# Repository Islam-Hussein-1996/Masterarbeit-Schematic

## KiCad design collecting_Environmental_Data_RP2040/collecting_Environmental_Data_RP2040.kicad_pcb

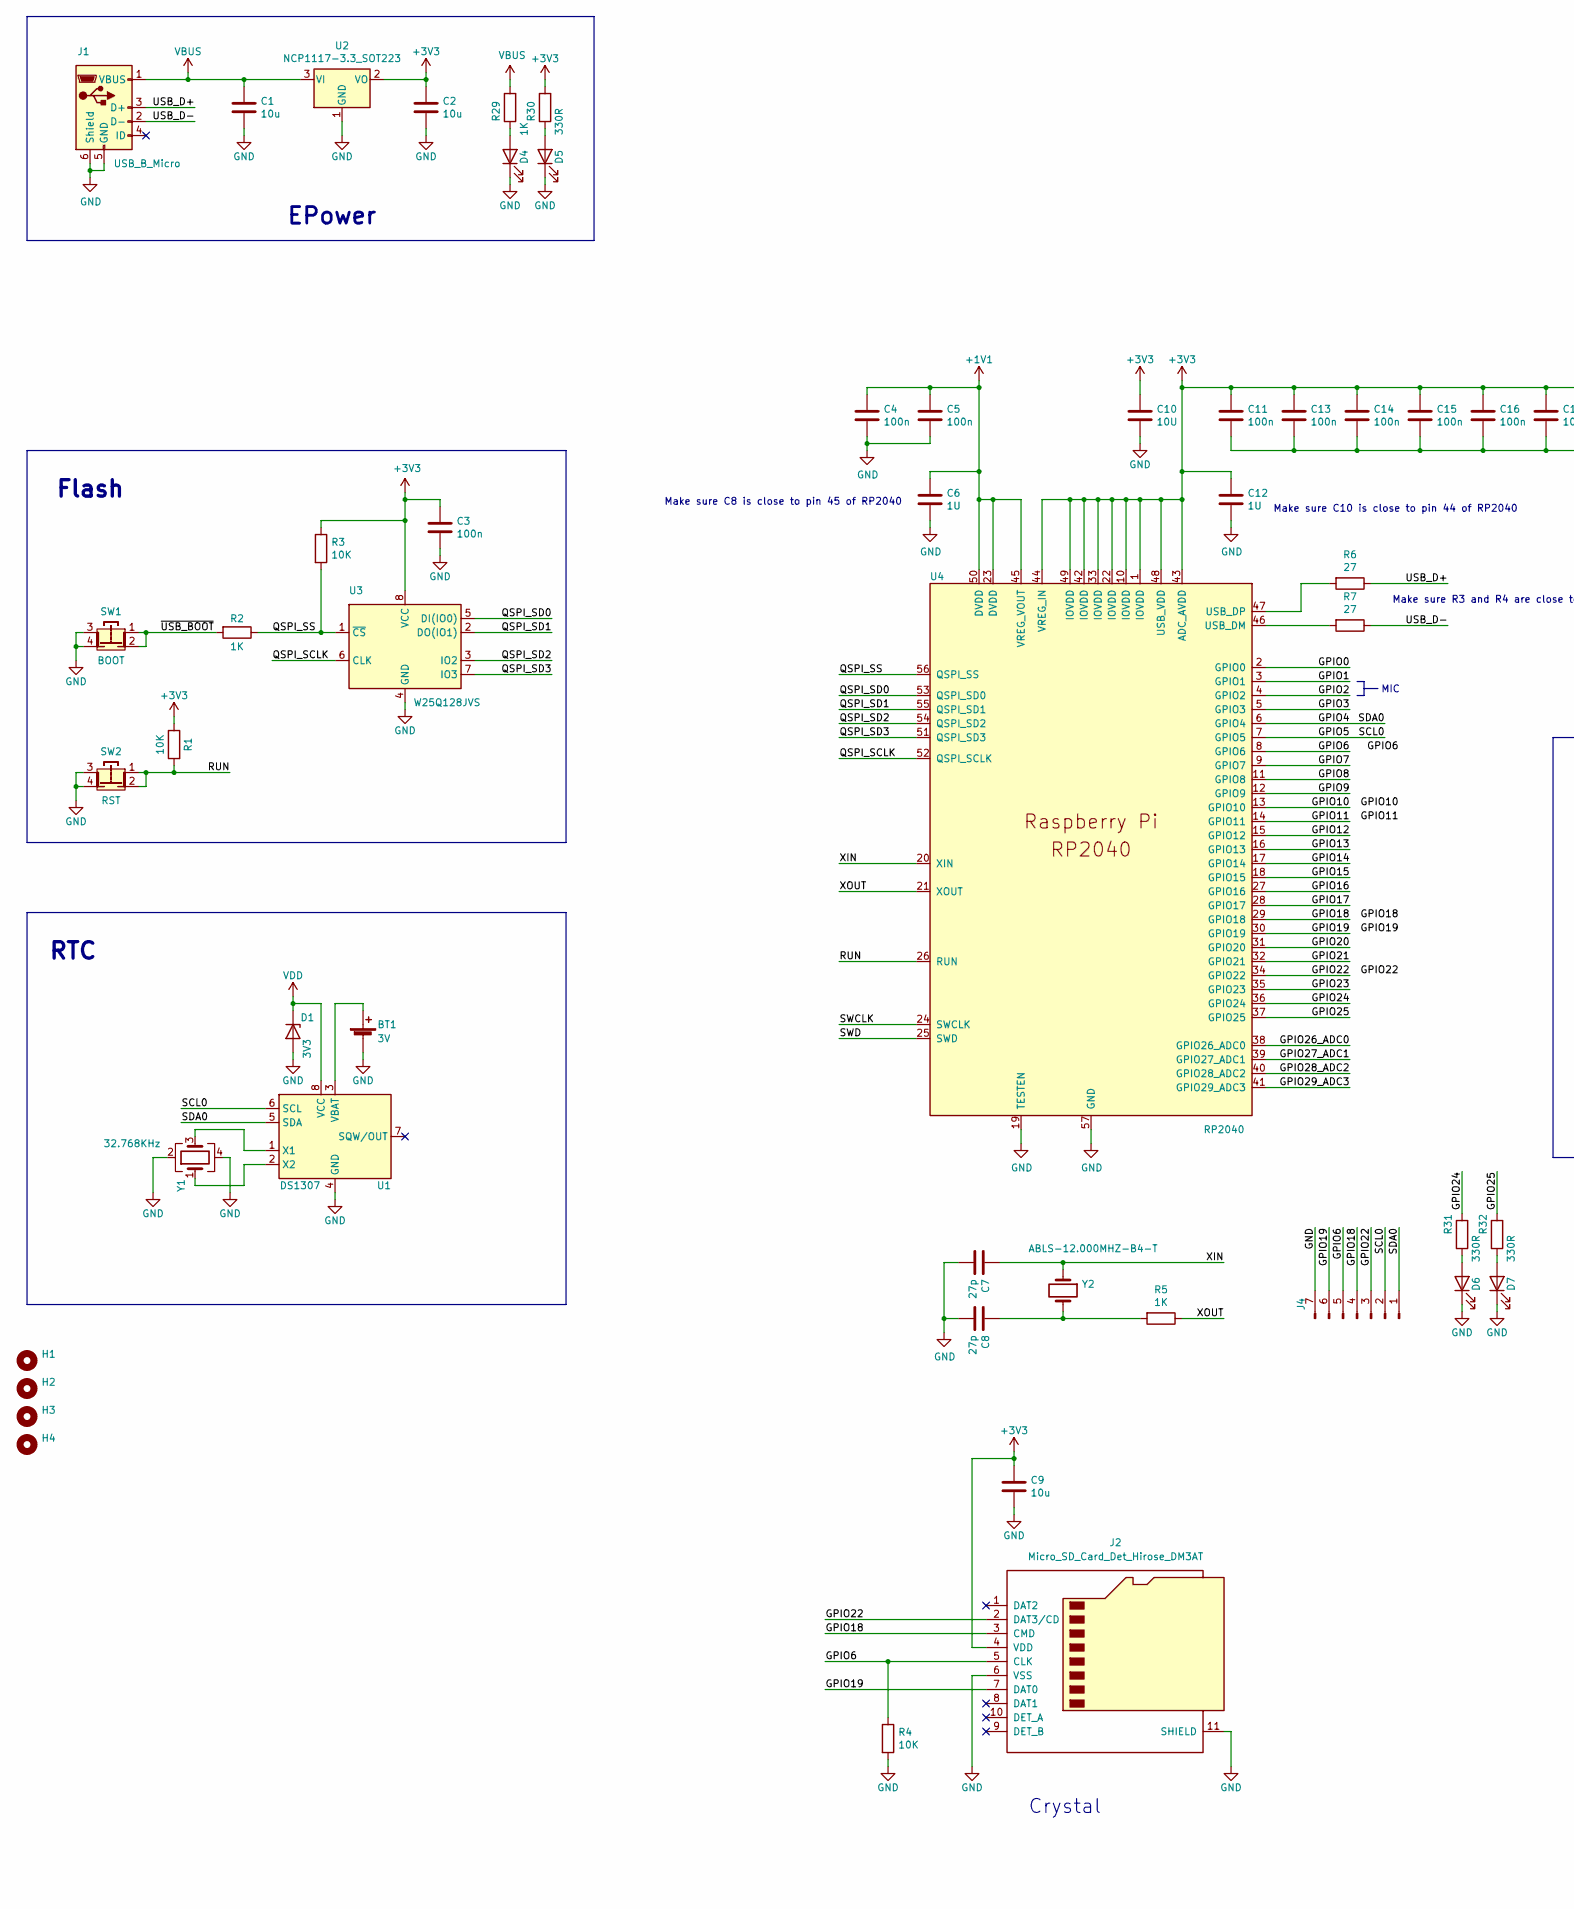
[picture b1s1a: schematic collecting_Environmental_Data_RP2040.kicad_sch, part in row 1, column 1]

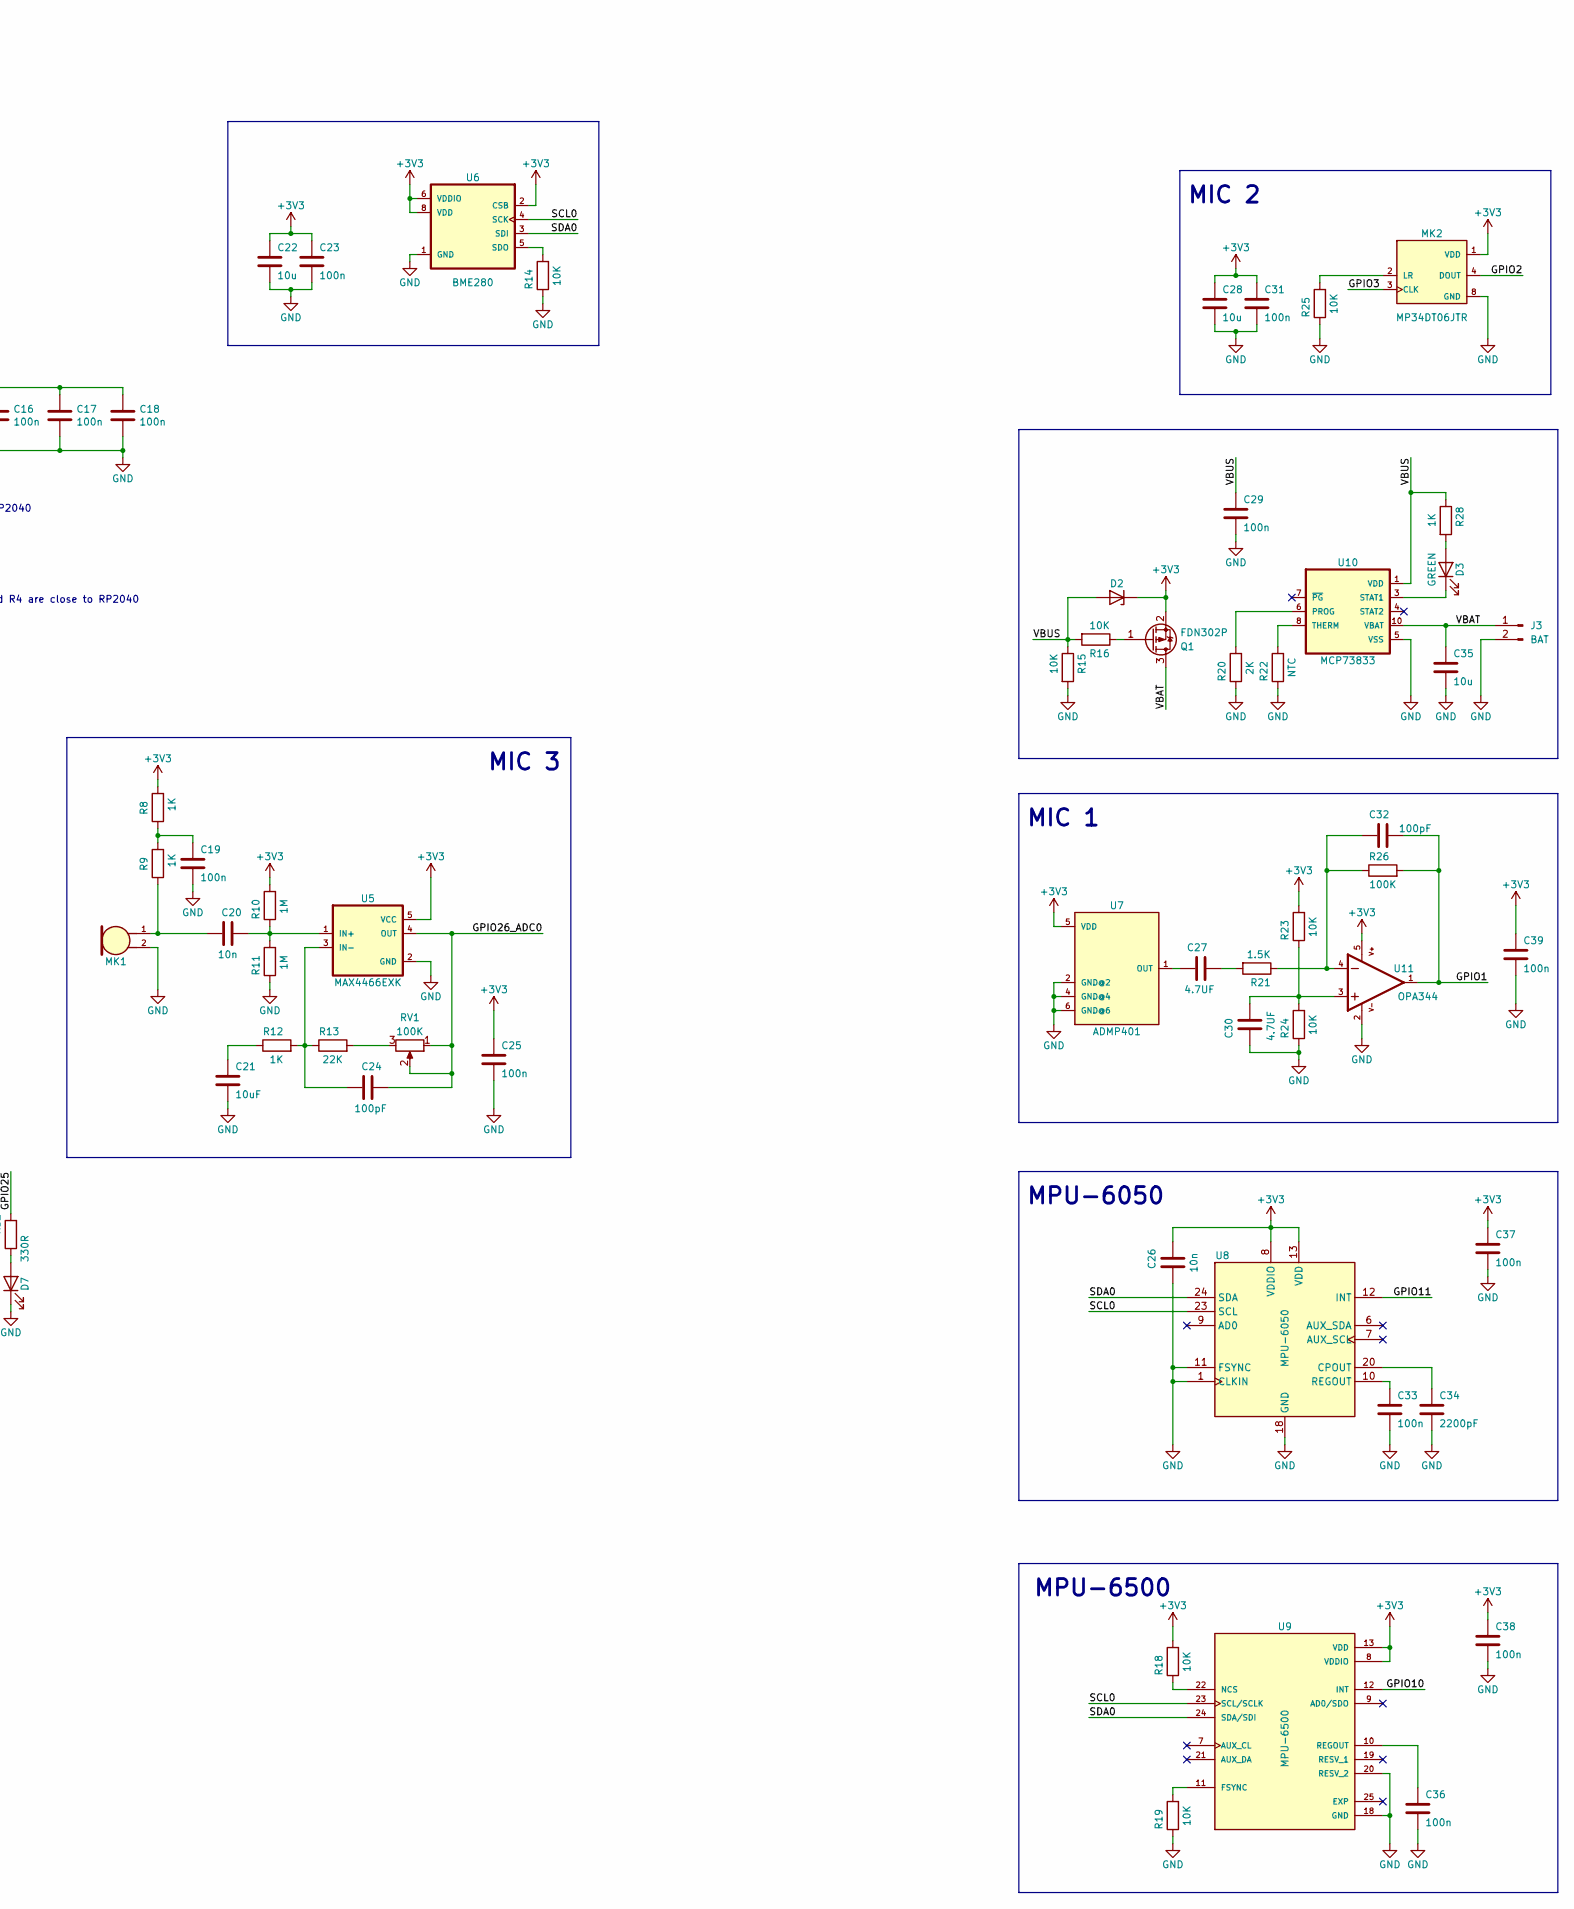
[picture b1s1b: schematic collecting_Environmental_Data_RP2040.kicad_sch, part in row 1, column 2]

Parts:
BT1: 3V; PinHeader_1x02_P2.54mm_Vertical
C1, C2, C9, C22, C28, C35: 10u; C_0805_2012Metric_Pad1.18x1.45mm_HandSolder
C3, C4, C5, C11, C13, C14, C15, C16, C17, C18, C19, C23, C25, C29, C31, C33, C36, C37, C38, C39: 100n; C_0603_1608Metric_Pad1.08x0.95mm_HandSolder
C6, C12: 1U; C_0603_1608Metric_Pad1.08x0.95mm_HandSolder
C7, C8: 27p; C_0603_1608Metric_Pad1.08x0.95mm_HandSolder
C10: 10U; C_0805_2012Metric_Pad1.18x1.45mm_HandSolder
C20, C26: 10n; C_0603_1608Metric_Pad1.08x0.95mm_HandSolder
C21: 10uF; C_0805_2012Metric_Pad1.18x1.45mm_HandSolder
C24, C32: 100pF; C_0603_1608Metric_Pad1.08x0.95mm_HandSolder
C27, C30: 4.7UF; C_0603_1608Metric_Pad1.08x0.95mm_HandSolder
C34: 2200pF; C_0603_1608Metric_Pad1.08x0.95mm_HandSolder
D1: 3V3; D_SOD-123
D2: D_Zener; D_SOD-123
D3: GREEN; LED_0805_2012Metric_Pad1.15x1.40mm_HandSolder
D4, D5, D6, D7: LED; LED_0805_2012Metric_Pad1.15x1.40mm_HandSolder
H1, H2, H3, H4: MountingHole; MountingHole_2.7mm_M2.5
J1: USB_B_Micro; USB_Micro-B_Molex-105017-0001
J2: Micro_SD_Card_Det_Hirose_DM3AT; microSD_HC_Molex_104031-0811
J3: BAT; PinHeader_1x02_P2.54mm_Vertical
J4: Conn_01x07_Male; PinHeader_1x07_P2.54mm_Vertical
MK1: CMA-4544PF-W; MIC_CMA-4544PF-W
MK2: MP34DT06JTR; MIC_MP34DT06JTR
Q1: FDN302P; SOT-23
R1, R3, R4, R14, R15, R16, R18, R19, R23, R24, R25: 10K; R_0603_1608Metric_Pad0.98x0.95mm_HandSolder
R2, R5, R8, R9, R12, R28, R29: 1K; R_0603_1608Metric_Pad0.98x0.95mm_HandSolder
R6, R7: 27; R_0603_1608Metric_Pad0.98x0.95mm_HandSolder
R10, R11: 1M; R_0603_1608Metric_Pad0.98x0.95mm_HandSolder
R13: 22K; R_0603_1608Metric_Pad0.98x0.95mm_HandSolder
R20: 2K; R_0603_1608Metric_Pad0.98x0.95mm_HandSolder
R21: 1.5K; R_0603_1608Metric_Pad0.98x0.95mm_HandSolder
R22: NTC; R_0603_1608Metric_Pad0.98x0.95mm_HandSolder
R26: 100K; R_0603_1608Metric_Pad0.98x0.95mm_HandSolder
R30, R31, R32: 330R; R_0603_1608Metric_Pad0.98x0.95mm_HandSolder
RV1: 100K; Potentiometer_Bourns_TC33X_Vertical
SW1: BOOT; SW_Push_4X4mm
SW2: RST; SW_Push_4X4mm
U1: DS1307; SOIC-8_3.9x4.9mm_P1.27mm
U2: NCP1117-3.3_SOT223; SOT-223-3_TabPin2
U3: W25Q128JVS; SOIC-8_5.23x5.23mm_P1.27mm
U4: RP2040; RP2040-QFN-56
U5: MAX4466EXK; SOT-353_SC-70-5
U6: BME280
U7: ADMP401
U8: MPU-6050; InvenSense_QFN-24_4x4mm_P0.5mm
U9: MPU-6500; QFN40P300X300X95-25N
U10: MCP73833; MSOP-10_3x3mm_P0.5mm
U11: OPA344; SOT-23-5
Y1: 32.768KHz
Y2: ABLS-12.000MHZ-B4-T; Crystal_SMD_ECS_CSM3X-2Pin_7.6x4.1mm

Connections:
+1V1: C4.1, C5.1, C6.1, U4.23 (DVDD), U4.45 (VREG_VOUT), U4.50 (DVDD)
+3V3: C2.1, C3.1, C9.1, C10.1, C11.1, C12.1, C13.1, C14.1, C15.1, C16.1, C17.1, C18.1, C22.1, C23.1, C25.1, C26.1, C28.1, C31.1, C37.1, C38.1, C39.1, D2.1 (K), J2.4 (VDD), MK2.1 (VDD), Q1.2 (S), R1.1, R3.1, R8.2, R10.2, R18.2, R23.2, R30.2, U2.2 (VO), U3.8 (VCC), U4.1 (IOVDD), U4.10 (IOVDD), U4.22 (IOVDD), U4.33 (IOVDD), U4.42 (IOVDD), U4.43 (ADC_AVDD), U4.44 (VREG_IN), U4.48 (USB_VDD), U4.49 (IOVDD), U5.5 (VCC), U6.2 (CSB), U6.6 (VDDIO), U6.8 (VDD), U7.5 (VDD), U8.8 (VDDIO), U8.13 (VDD), U9.8 (VDDIO), U9.13 (VDD), U11.5
/GPIO0: U4.2 (GPIO0)
/GPIO1: C32.2, R26.2, U4.3 (GPIO1), U11.1
/GPIO2: MK2.4 (DOUT), U4.4 (GPIO2)
/GPIO3: MK2.3 (CLK), U4.5 (GPIO3)
/GPIO4: J4.1, U1.5 (SDA), U4.6 (GPIO4), U6.3 (SDI), U8.24 (SDA), U9.24 (SDA/SDI)
/GPIO5: J4.2, U1.6 (SCL), U4.7 (GPIO5), U6.4 (SCK), U8.23 (SCL), U9.23 (SCL/SCLK)
/GPIO6: J2.5 (CLK), J4.5, R4.1, U4.8 (GPIO6)
/GPIO7: U4.9 (GPIO7)
/GPIO8: U4.11 (GPIO8)
/GPIO9: U4.12 (GPIO9)
/GPIO10: U4.13 (GPIO10), U9.12 (INT)
/GPIO11: U4.14 (GPIO11), U8.12 (INT)
/GPIO12: U4.15 (GPIO12)
/GPIO13: U4.16 (GPIO13)
/GPIO14: U4.17 (GPIO14)
/GPIO15: U4.18 (GPIO15)
/GPIO16: U4.27 (GPIO16)
/GPIO17: U4.28 (GPIO17)
/GPIO18: J2.3 (CMD), J4.4, U4.29 (GPIO18)
/GPIO19: J2.7 (DAT0), J4.6, U4.30 (GPIO19)
/GPIO20: U4.31 (GPIO20)
/GPIO21: U4.32 (GPIO21)
/GPIO22: J2.2 (DAT3/CD), J4.3, U4.34 (GPIO22)
/GPIO23: U4.35 (GPIO23)
/GPIO24: R31.2, U4.36 (GPIO24)
/GPIO25: R32.2, U4.37 (GPIO25)
/GPIO26_ADC0: C24.1, RV1.1, RV1.2, U4.38 (GPIO26_ADC0), U5.4 (OUT)
/GPIO27_ADC1: U4.39 (GPIO27_ADC1)
/GPIO28_ADC2: U4.40 (GPIO28_ADC2)
/GPIO29_ADC3: U4.41 (GPIO29_ADC3)
/QSPI_SCLK: U3.6 (CLK), U4.52 (QSPI_SCLK)
/QSPI_SD0: U3.5 (DI(IO0)), U4.53 (QSPI_SD0)
/QSPI_SD1: U3.2 (DO(IO1)), U4.55 (QSPI_SD1)
/QSPI_SD2: U3.3 (IO2), U4.54 (QSPI_SD2)
/QSPI_SD3: U3.7 (IO3), U4.51 (QSPI_SD3)
/QSPI_SS: R2.1, R3.2, U3.1 (~CS), U4.56 (QSPI_SS)
/RUN: R1.2, SW2.1, SW2.2, U4.26 (RUN)
/SWCLK: U4.24 (SWCLK)
/SWD: U4.25 (SWD)
/USB_D+: J1.3 (D+), R6.1
/USB_D-: J1.2 (D-), R7.1
/VBAT: C35.1, J3.1, Q1.3 (D), U10.9 (VBAT), U10.10 (VBAT)
/XIN: C7.1, U4.20 (XIN), Y2.1
/XOUT: R5.1, U4.21 (XOUT)
/~USB_BOOT: R2.2, SW1.1, SW1.2
GND: BT1.2 (-), C1.2, C2.2, C3.2, C4.2, C5.2, C6.2, C7.2, C8.2, C9.2, C10.2, C11.2, C12.2, C13.2, C14.2, C15.2, C16.2, C17.2, C18.2, C19.2, C21.2, C22.2, C23.2, C25.2, C26.2, C28.2, C29.2, C30.1, C31.2, C33.2, C34.2, C35.2, C36.2, C37.2, C38.2, C39.2, D1.2 (A), D4.1 (K), D5.1 (K), D6.1 (K), D7.1 (K), J1.5 (GND), J1.6 (Shield), J2.6 (VSS), J2.11 (SHIELD), J3.2, J4.7, MK1.2, MK2.5 (GND), MK2.6 (GND), MK2.7 (GND), MK2.8 (GND), R4.2, R11.1, R14.1, R15.2, R19.1, R20.1, R22.1, R24.1, R25.1, SW1.3, SW1.4, SW2.3, SW2.4, U1.4 (GND), U2.1 (GND), U3.4 (GND), U4.19 (TESTEN), U4.57 (GND), U5.2 (GND), U6.1 (GND), U6.7 (GND), U7.2 (GND@2), U7.4 (GND@4), U7.6 (GND@6), U8.1 (CLKIN), U8.11 (FSYNC), U8.18 (GND), U9.18 (GND), U9.20 (RESV_2), U10.5 (VSS), U11.2, Y1.2, Y1.4
unnamed: BT1.1 (+), U1.3 (VBAT)
unnamed: C8.1, R5.2, Y2.2
unnamed: C19.1, R8.1, R9.2
unnamed: C20.1, R10.1, R11.2, U5.1 (IN+)
unnamed: C20.2, MK1.1, R9.1
unnamed: C21.1, R12.1
unnamed: C24.2, R12.2, R13.1, U5.3 (IN-)
unnamed: C27.1, U7.1 (OUT)
unnamed: C27.2, R21.2
unnamed: C30.2, R23.1, R24.2, U11.3
unnamed: C32.1, R21.1, R26.1, U11.4
unnamed: C33.1, U8.10 (REGOUT)
unnamed: C34.1, U8.20 (CPOUT)
unnamed: C36.1, U9.10 (REGOUT)
unnamed: D3.1 (K), U10.3 (STAT1)
unnamed: D3.2 (A), R28.2
unnamed: D4.2 (A), R29.1
unnamed: D5.2 (A), R30.1
unnamed: D6.2 (A), R31.1
unnamed: D7.2 (A), R32.1
unnamed: MK2.2 (LR), R25.2
unnamed: Q1.1 (G), R16.1
unnamed: R6.2, U4.47 (USB_DP)
unnamed: R7.2, U4.46 (USB_DM)
unnamed: R13.2, RV1.3
unnamed: R14.2, U6.5 (SDO)
unnamed: R18.1, U9.22 (NCS)
unnamed: R19.2, U9.11 (FSYNC)
unnamed: R20.2, U10.6 (PROG)
unnamed: R22.2, U10.8 (THERM)
unnamed: U1.1 (X1), Y1.3
unnamed: U1.2 (X2), Y1.1

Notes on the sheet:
Crystal
MIC 3
Make sure R3 and R4 are close to RP2040
Make sure C10 is close to pin 44 of RP2040
MIC 2
MPU-6500
MIC
MPU-6050
Flash
RTC
Make sure C8 is close to pin 45 of RP2040
MIC 1
EPower

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
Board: 2 copper layers, 104 parts (41 on the bottom side), 63 nets, no tracks yet.

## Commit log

2023-01-02 Layout Started Old commits Lost
